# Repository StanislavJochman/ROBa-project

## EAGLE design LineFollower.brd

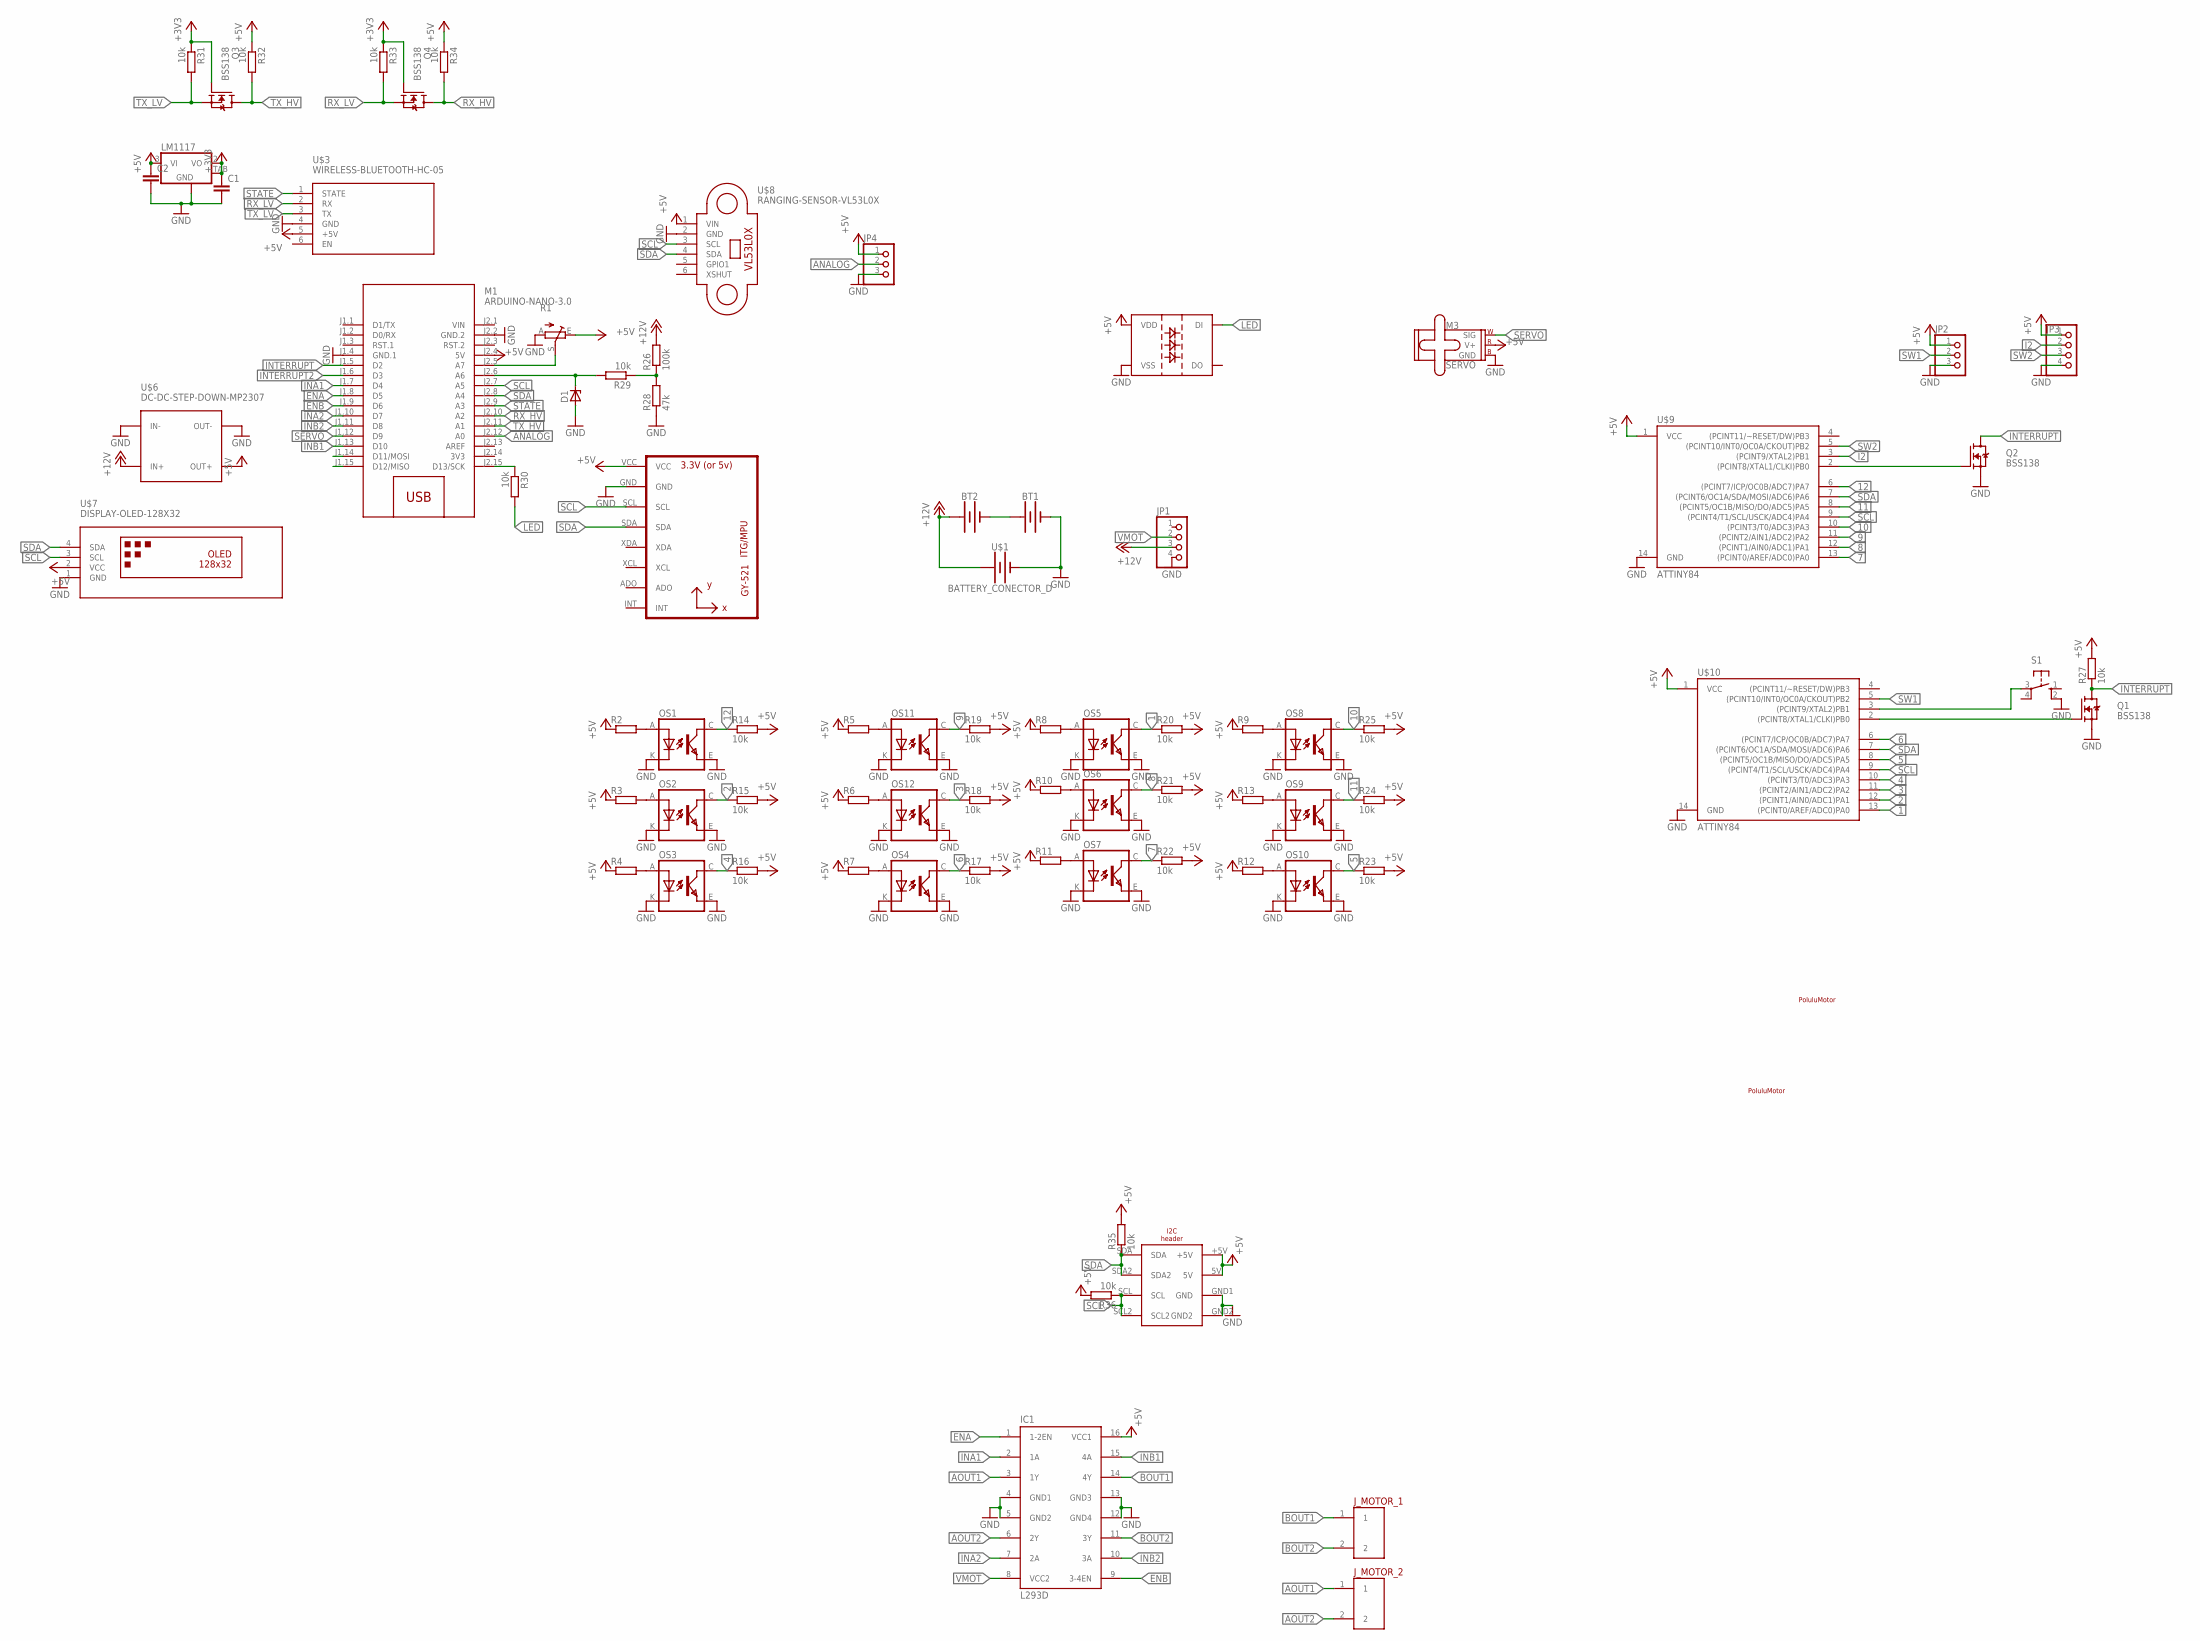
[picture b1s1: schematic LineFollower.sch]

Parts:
BT1, BT2: BATTERY-AA_KIT; BATTERY-AA-KIT
C1, C2: C-EUC1206; C1206
D1: ZENER-DIODESOD80C; SOD80C
IC1: L293D; L293
JP1, JP3: PINHD-1X4; 1X04
JP2, JP4: PINHD-1X3; 1X03
J_MOTOR_1, J_MOTOR_2: MOTOR_CONNECTOR; MOTOR_CONNECTOR_FOOTPRINT
LED1: WS2812B
M1: ARDUINO-NANO-3.0
M3: SERVO; 1X03
OS1, OS2, OS3, OS4, OS5, OS6, OS7, OS8, OS9, OS10, OS11, OS12: TCRT5000
Q1, Q2, Q3, Q4: BSS138; SOT23
R1: TRIM_EU-RJ9W; RJ9W
R2, R3, R4, R5, R6, R7, R8, R9, R10, R11, R12, R13: R-EU_M1206; M1206
R14, R15, R16, R17, R18, R19, R20, R21, R22, R23, R24, R25, R27, R29, R30, R31, R32, R33, R34, R35, R36: 10k; M1206
R26: 100k; M1206
R28: 47k; M1206
S1: 10-XX; B3F-10XX
U1: MPU-6050MPU6050; MPU-6050
U$1: BATTERY_CONECTOR_D
U$2: I2C_HEADER; I2_HEADER
U$3: WIRELESS-BLUETOOTH-HC-05
U$4: LM1117
U$6: DC-DC-STEP-DOWN-MP2307
U$7: DISPLAY-OLED-128X32
U$8: RANGING-SENSOR-VL53L0X
U$9, U$10: ATTINY84; SO14
U$12, U$13: POLULU_MOTOR

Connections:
1: OS5.C (COLLECTOR), R20.1, U$10.13 ((PCINT0/AREF/ADC0)PA0)
2: OS2.C (COLLECTOR), R15.1, U$10.12 ((PCINT1/AIN0/ADC1)PA1)
3: OS12.C (COLLECTOR), R18.1, U$10.11 ((PCINT2/AIN1/ADC2)PA2)
3V3: M1.J2.14 (3V3)
4: OS3.C (COLLECTOR), R16.1, U$10.10 ((PCINT3/T0/ADC3)PA3)
5: OS10.C (COLLECTOR), R23.1, U$10.8 ((PCINT5/OC1B/MISO/DO/ADC5)PA5)
6: OS4.C (COLLECTOR), R17.1, U$10.6 ((PCINT7/ICP/OC0B/ADC7)PA7)
7: OS7.C (COLLECTOR), R22.1, U$9.13 ((PCINT0/AREF/ADC0)PA0)
8: OS6.C (COLLECTOR), R21.1, U$9.12 ((PCINT1/AIN0/ADC1)PA1)
9: OS11.C (COLLECTOR), R19.1, U$9.11 ((PCINT2/AIN1/ADC2)PA2)
10: OS8.C (COLLECTOR), R25.1, U$9.10 ((PCINT3/T0/ADC3)PA3)
11: OS9.C (COLLECTOR), R24.1, U$9.8 ((PCINT5/OC1B/MISO/DO/ADC5)PA5)
12: OS1.C (COLLECTOR), R14.1, U$9.6 ((PCINT7/ICP/OC0B/ADC7)PA7)
+3V3: C1.1, Q3.1 (G), Q4.1 (G), R31.1, R33.1, U$4.2 (VO), U$4.TAB (OUT)
+5V: C2.1, IC1.16 (VCC1), JP2.1, JP3.1, JP4.1, LED1.1 (VDD), M1.J2.4 (5V), M3.2 (V+), R1.E, R2.1, R3.1, R4.1, R5.1, R6.1, R7.1, R8.1, R9.1, R10.1, R11.1, R12.1, R13.1, R14.2, R15.2, R16.2, R17.2, R18.2, R19.2, R20.2, R21.2, R22.2, R23.2, R24.2, R25.2, R27.2, R32.1, R34.1, R35.2, R36.2, U1.VCC, U$2.5V, U$2.+5V, U$3.5 (+5V), U$4.3 (VI), U$6.OUT+, U$7.2 (VCC), U$8.1 (VIN), U$9.1 (VCC), U$10.1 (VCC)
+12V: BT2.PWR@1 (+), JP1.3, R26.2, U$1.+, U$6.IN+
ANALOG: JP4.2, M1.J2.12 (A0)
AOUT1: IC1.3 (1Y), J_MOTOR_2.1
AOUT2: IC1.6 (2Y), J_MOTOR_2.2
BOUT1: IC1.14 (4Y), J_MOTOR_1.1
BOUT2: IC1.11 (3Y), J_MOTOR_1.2
ENA: IC1.1 (1-2EN), M1.J1.8 (D5)
ENB: IC1.9 (3-4EN), M1.J1.9 (D6)
GND: BT1.GND@1 (-), C1.2, C2.2, D1.A, IC1.4 (GND1), IC1.5 (GND2), IC1.12 (GND4), IC1.13 (GND3), JP1.4, JP2.3, JP3.4, JP4.3, LED1.3 (VSS), M1.J1.4 (GND.1), M1.J2.2 (GND.2), M3.3 (GND), OS1.E (EMITTER), OS1.K (CATHODE), OS2.E (EMITTER), OS2.K (CATHODE), OS3.E (EMITTER), OS3.K (CATHODE), OS4.E (EMITTER), OS4.K (CATHODE), OS5.E (EMITTER), OS5.K (CATHODE), OS6.E (EMITTER), OS6.K (CATHODE), OS7.E (EMITTER), OS7.K (CATHODE), OS8.E (EMITTER), OS8.K (CATHODE), OS9.E (EMITTER), OS9.K (CATHODE), OS10.E (EMITTER), OS10.K (CATHODE), OS11.E (EMITTER), OS11.K (CATHODE), OS12.E (EMITTER), OS12.K (CATHODE), Q1.2 (S), Q2.2 (S), R1.A, R28.1, S1.2 (S1), U1.GND, U$1.-, U$2.GND1 (GND), U$2.GND2, U$3.4 (GND), U$4.1 (GND), U$6.IN-, U$6.OUT-, U$7.1 (GND), U$8.2 (GND), U$9.14 (GND), U$10.14 (GND)
I2: JP3.2, U$9.3 ((PCINT9/XTAL2)PB1)
INA1: IC1.2 (1A), M1.J1.7 (D4)
INA2: IC1.7 (2A), M1.J1.10 (D7)
INB1: IC1.15 (4A), M1.J1.13 (D10)
INB2: IC1.10 (3A), M1.J1.11 (D8)
INTERRUPT: M1.J1.5 (D2), Q1.3 (D), Q2.3 (D), R27.1
INTERRUPT2: M1.J1.6 (D3)
LED: LED1.4 (DI), R30.2
unnamed: M1.J2.5 (A7), R1.S
unnamed: BT1.PWR@1 (+), BT2.GND@1 (-)
unnamed: Q1.1 (G), U$10.2 ((PCINT8/XTAL1/CLKI)PB0)
unnamed: Q2.1 (G), U$9.2 ((PCINT8/XTAL1/CLKI)PB0)
unnamed: S1.3, U$10.3 ((PCINT9/XTAL2)PB1)
unnamed: R26.1, R28.2, R29.1
unnamed: OS1.A (ANODE), R2.2
unnamed: OS2.A (ANODE), R3.2
unnamed: OS3.A (ANODE), R4.2
unnamed: OS11.A (ANODE), R5.2
unnamed: OS12.A (ANODE), R6.2
unnamed: OS4.A (ANODE), R7.2
unnamed: OS5.A (ANODE), R8.2
unnamed: OS6.A (ANODE), R10.2
unnamed: OS7.A (ANODE), R11.2
unnamed: OS10.A (ANODE), R12.2
unnamed: OS9.A (ANODE), R13.2
unnamed: OS8.A (ANODE), R9.2
unnamed: D1.C, M1.J2.6 (A6), R29.2
unnamed: M1.J2.15 (D13/SCK), R30.1
RX_HV: M1.J2.10 (A2), Q4.3 (D), R34.2
RX_LV: Q4.2 (S), R33.2, U$3.2 (RX)
SCL: M1.J2.7 (A5), R36.1, U1.SCL, U$2.SCL, U$2.SCL2, U$7.3 (SCL), U$8.3 (SCL), U$9.9 ((PCINT4/T1/SCL/USCK/ADC4)PA4), U$10.9 ((PCINT4/T1/SCL/USCK/ADC4)PA4)
SDA: M1.J2.8 (A4), R35.1, U1.SDA, U$2.SDA, U$2.SDA2, U$7.4 (SDA), U$8.4 (SDA), U$9.7 ((PCINT6/OC1A/SDA/MOSI/ADC6)PA6), U$10.7 ((PCINT6/OC1A/SDA/MOSI/ADC6)PA6)
SERVO: M1.J1.12 (D9), M3.1 (SIG)
STATE: M1.J2.9 (A3), U$3.1 (STATE)
SW1: JP2.2, U$10.5 ((PCINT10/INT0/OC0A/CKOUT)PB2)
SW2: JP3.3, U$9.5 ((PCINT10/INT0/OC0A/CKOUT)PB2)
TX_HV: M1.J2.11 (A1), Q3.3 (D), R32.2
TX_LV: Q3.2 (S), R31.2, U$3.3 (TX)
VIN: M1.J2.1 (VIN)
VMOT: IC1.8 (VCC2), JP1.2

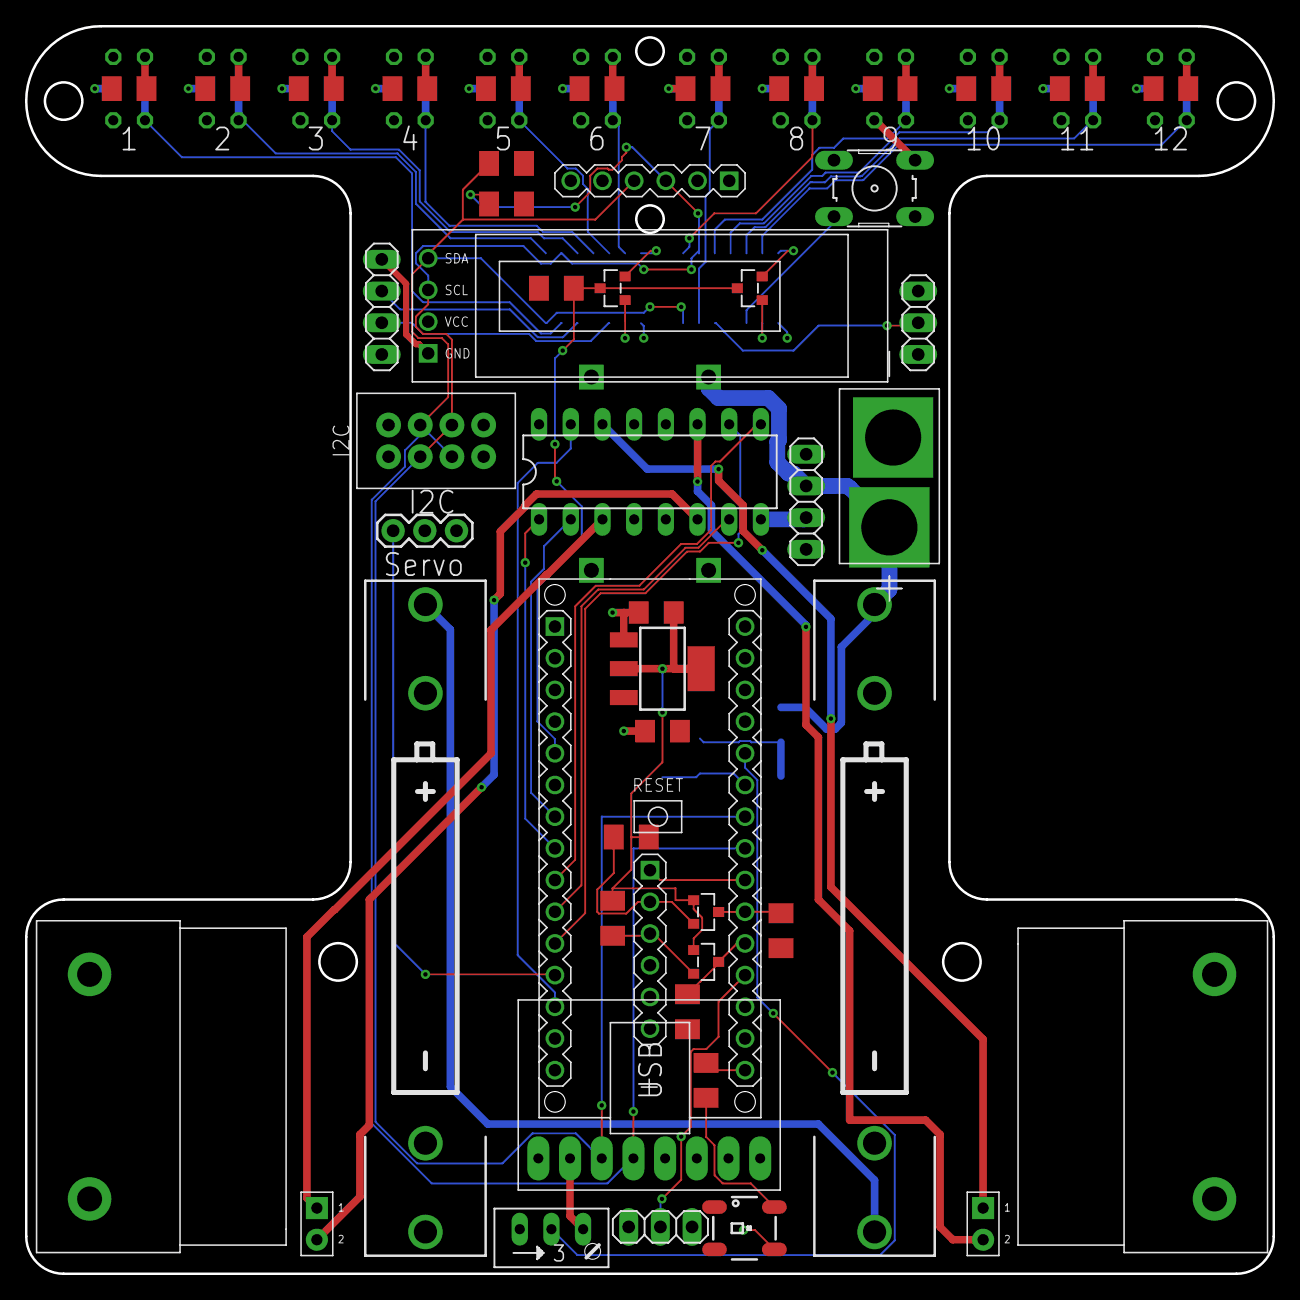
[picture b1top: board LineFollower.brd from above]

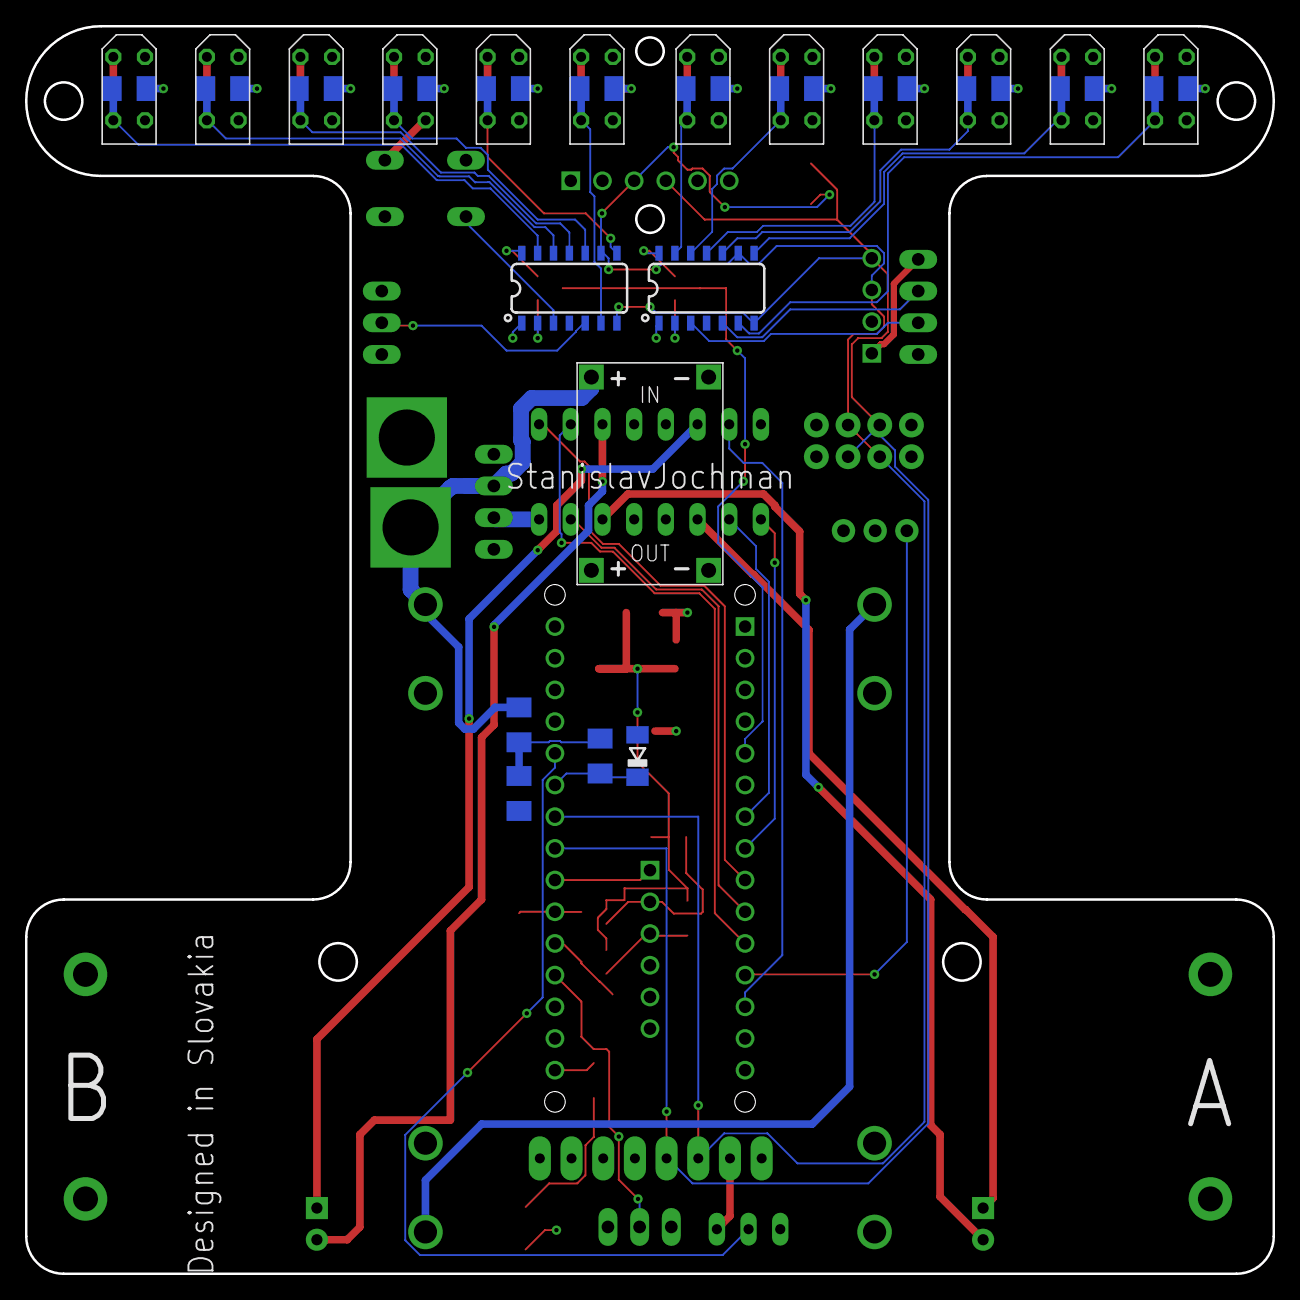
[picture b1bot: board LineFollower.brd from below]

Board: 2 copper layers, 100.0 x 100.0 mm, 80 parts (19 on the bottom side), 61 nets.

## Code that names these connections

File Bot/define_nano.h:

/////////////////////////////////////////////////////////
#define button 4
/////////////////////////////////////////////////////////
/////////////////////////////////////////////////////////
#define ENB 6
#define ENA 5
#define INB2 8
#define INB1 10 
#define INA2 7
#define INA1 4
#define servo_pin 9
#define pot A7

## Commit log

2023-11-16 roba changes
2024-01-25 final commit

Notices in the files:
parts and their libraries:
diy-modules: Released under the Creative Commons Attribution 4.0 International License: http://creativecommons.org/licenses/by/4.0
SparkFun-IC-Microcontroller: Licensing: Creative Commons ShareAlike 4.0 International - https://creativecommons.org/licenses/by-sa/4.0
